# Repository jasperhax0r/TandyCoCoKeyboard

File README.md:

<!-- 
[![Contributors][contributors-shield]][contributors-url]
[![Forks][forks-shield]][forks-url]
[![Stargazers][stars-shield]][stars-url]
[![Issues][issues-shield]][issues-url]
[![License][license-shield]][license-url]
[![LinkedIn][linkedin-shield]][linkedin-url] -->

![Tandy CoCo2 Keyboard][product-screenshot]

* [Choose an Open Source License](https://choosealicense.com)
<!--  * [Img Shields](https://shields.io) -->
* [GitHub Pages](https://pages.github.com)

<!-- [contributors-shield]: https://img.shields.io/github/contributors/othneildrew/Best-README-Template.svg?style=for-the-badge
[contributors-url]: https://github.com/jasperhax0r/TandyCoCoKeyboard/graphs/contributors
[forks-shield]: https://img.shields.io/github/forks/othneildrew/Best-README-Template.svg?style=for-the-badge
[forks-url]: https://github.com/jasperhax0r/TandyCoCoKeyboard/network/members
[stars-shield]: https://img.shields.io/github/stars/othneildrew/Best-README-Template.svg?style=for-the-badge
[stars-url]: https://github.com/jasperhax0r/TandyCoCoKeyboard/stargazers
[issues-shield]: https://img.shields.io/github/issues/othneildrew/Best-README-Template.svg?style=for-the-badge
[issues-url]: https://github.com/jasperhax0r/TandyCoCoKeyboard/issues
[license-shield]: https://img.shields.io/github/license/jasperhax0r/TandyCoCoKeyboard?style=for-the-badge
[license-url]: https://github.com/jasperhax0r/TandyCoCoKeyboard/blob/main/LICENSE
[linkedin-shield]: https://img.shields.io/badge/-LinkedIn-black.svg?style=for-the-badge&logo=linkedin&colorB=555
[linkedin-url]: https://linkedin.com/in/othneildrew](https://www.linkedin.com/in/jasper-johnson-922b7330/
 -->
[product-screenshot]: images/3dview.png

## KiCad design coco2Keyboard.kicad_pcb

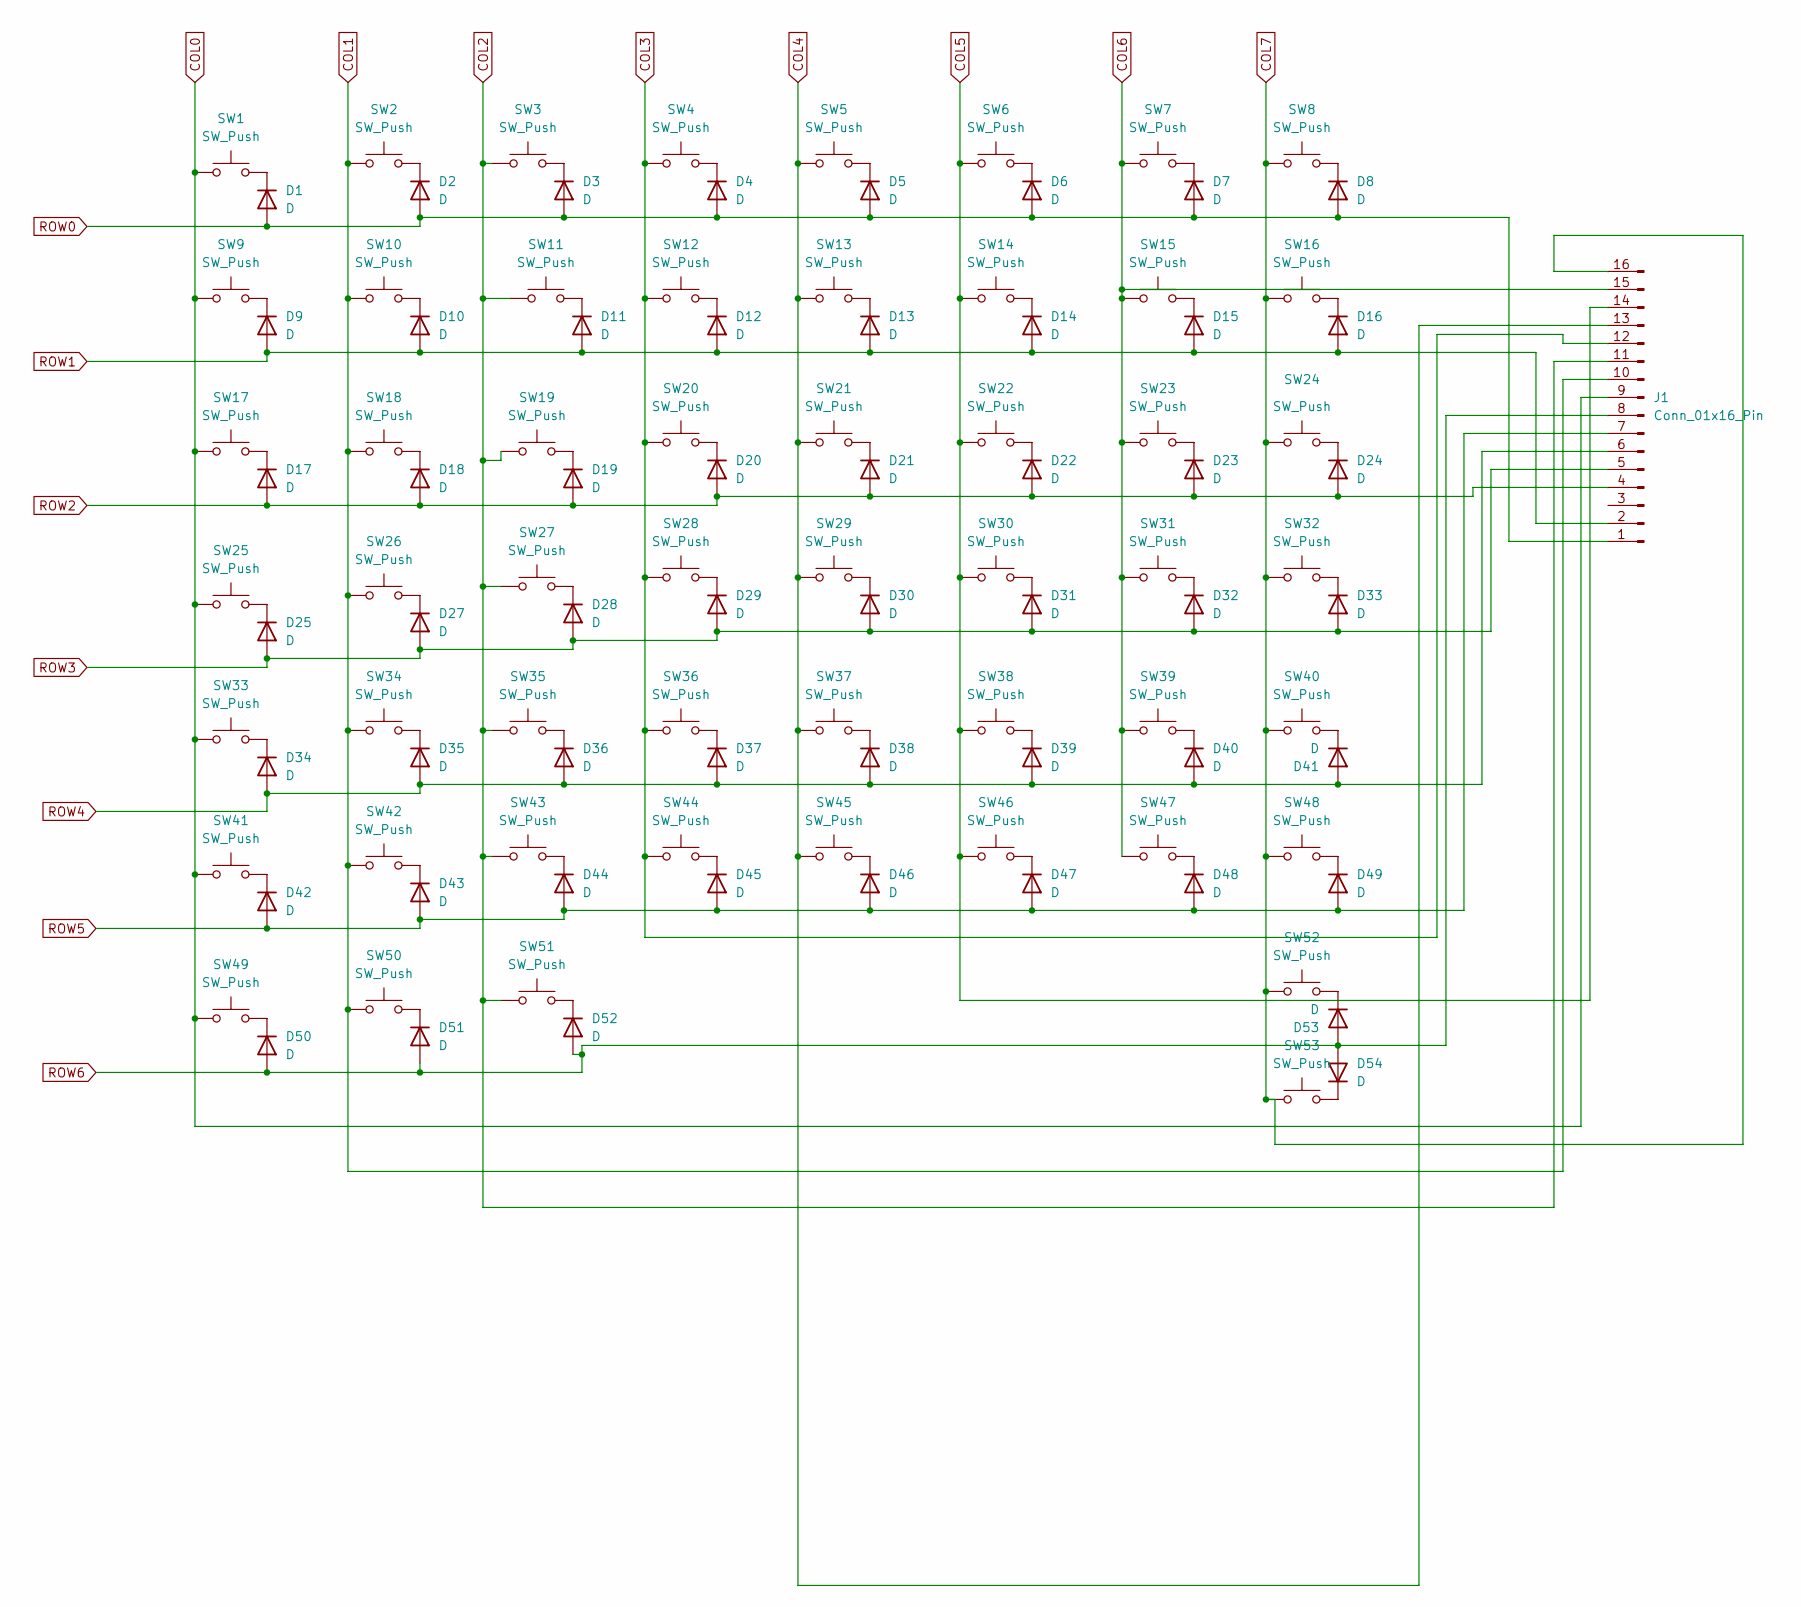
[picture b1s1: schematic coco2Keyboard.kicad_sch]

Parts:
D1, D2, D3, D4, D5, D6, D7, D8, D9, D10, D11, D12, D13, D14, D15, D16, D17, D18, D19, D20, D21, D22, D23, D24, D25, D27, D28, D29, D30, D31, D32, D33, D34, D35, D36, D37, D38, D39, D40, D41, D42, D43, D44, D45, D46, D47, D48, D49, D50, D51, D52, D53, D54: D; D_SOD-123
J1: Conn_01x16_Pin; PinHeader_1x16_P2.54mm_Horizontal
SW1, SW2, SW3, SW4, SW5, SW6, SW7, SW8, SW9, SW10, SW11, SW12, SW13, SW14, SW15, SW16, SW17, SW18, SW19, SW20, SW21, SW22, SW23, SW24, SW25, SW26, SW27, SW28, SW29, SW30, SW31, SW33, SW34, SW35, SW36, SW37, SW38, SW39, SW40, SW41, SW42, SW43, SW44, SW45, SW46, SW47, SW48, SW50, SW51: SW_Push; SW_Cherry_MX_1.00u_PCB
SW32: SW_Push; SW_Cherry_MX_6.25u_PCB
SW49: SW_Push; SW_Cherry_MX_2.25u_PCB
SW52, SW53: SW_Push; SW_Cherry_MX_1.75u_PCB

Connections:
COL0: J1.9, SW1.1, SW9.1, SW17.1, SW25.1, SW33.1, SW41.1, SW49.1
COL1: J1.10, SW2.1, SW10.1, SW18.1, SW26.1, SW34.1, SW42.1, SW50.1
COL2: J1.11, SW3.1, SW11.1, SW19.1, SW27.1, SW35.1, SW43.1, SW51.1
COL3: J1.12, SW4.1, SW12.1, SW20.1, SW28.1, SW36.1, SW44.1
COL4: J1.13, SW5.1, SW13.1, SW21.1, SW29.1, SW37.1, SW45.1
COL5: J1.14, SW6.1, SW14.1, SW22.1, SW30.1, SW38.1, SW46.1
COL6: J1.15, SW7.1, SW15.1, SW23.1, SW31.1, SW39.1, SW47.1
COL7: J1.16, SW8.1, SW16.1, SW24.1, SW32.1, SW40.1, SW48.1, SW52.1, SW53.1
unnamed: D1.1 (K), SW1.2
unnamed: D2.1 (K), SW2.2
unnamed: D3.1 (K), SW3.2
unnamed: D4.1 (K), SW4.2
unnamed: D5.1 (K), SW5.2
unnamed: D6.1 (K), SW6.2
unnamed: D7.1 (K), SW7.2
unnamed: D8.1 (K), SW8.2
unnamed: D9.1 (K), SW9.2
unnamed: D10.1 (K), SW10.2
unnamed: D11.1 (K), SW11.2
unnamed: D12.1 (K), SW12.2
unnamed: D13.1 (K), SW13.2
unnamed: D14.1 (K), SW14.2
unnamed: D15.1 (K), SW15.2
unnamed: D16.1 (K), SW16.2
unnamed: D17.1 (K), SW17.2
unnamed: D18.1 (K), SW18.2
unnamed: D19.1 (K), SW19.2
unnamed: D20.1 (K), SW20.2
unnamed: D21.1 (K), SW21.2
unnamed: D22.1 (K), SW22.2
unnamed: D23.1 (K), SW23.2
unnamed: D24.1 (K), SW24.2
unnamed: D25.1 (K), SW25.2
unnamed: D27.1 (K), SW26.2
unnamed: D28.1 (K), SW27.2
unnamed: D29.1 (K), SW28.2
unnamed: D30.1 (K), SW29.2
unnamed: D31.1 (K), SW30.2
unnamed: D32.1 (K), SW31.2
unnamed: D33.1 (K), SW32.2
unnamed: D34.1 (K), SW33.2
unnamed: D35.1 (K), SW34.2
unnamed: D36.1 (K), SW35.2
unnamed: D37.1 (K), SW36.2
unnamed: D38.1 (K), SW37.2
unnamed: D39.1 (K), SW38.2
unnamed: D40.1 (K), SW39.2
unnamed: D41.1 (K), SW40.2
unnamed: D42.1 (K), SW41.2
unnamed: D43.1 (K), SW42.2
unnamed: D44.1 (K), SW43.2
unnamed: D45.1 (K), SW44.2
unnamed: D46.1 (K), SW45.2
unnamed: D47.1 (K), SW46.2
unnamed: D48.1 (K), SW47.2
unnamed: D49.1 (K), SW48.2
unnamed: D50.1 (K), SW49.2
unnamed: D51.1 (K), SW50.2
unnamed: D52.1 (K), SW51.2
unnamed: D53.1 (K), SW52.2
unnamed: D54.1 (K), SW53.2
ROW0: D1.2 (A), D2.2 (A), D3.2 (A), D4.2 (A), D5.2 (A), D6.2 (A), D7.2 (A), D8.2 (A), J1.1
ROW1: D9.2 (A), D10.2 (A), D11.2 (A), D12.2 (A), D13.2 (A), D14.2 (A), D15.2 (A), D16.2 (A), J1.2
ROW2: D17.2 (A), D18.2 (A), D19.2 (A), D20.2 (A), D21.2 (A), D22.2 (A), D23.2 (A), D24.2 (A), J1.4
ROW3: D25.2 (A), D27.2 (A), D28.2 (A), D29.2 (A), D30.2 (A), D31.2 (A), D32.2 (A), D33.2 (A), J1.5
ROW4: D34.2 (A), D35.2 (A), D36.2 (A), D37.2 (A), D38.2 (A), D39.2 (A), D40.2 (A), D41.2 (A), J1.6
ROW5: D42.2 (A), D43.2 (A), D44.2 (A), D45.2 (A), D46.2 (A), D47.2 (A), D48.2 (A), D49.2 (A), J1.7
ROW6: D50.2 (A), D51.2 (A), D52.2 (A), D53.2 (A), D54.2 (A), J1.8

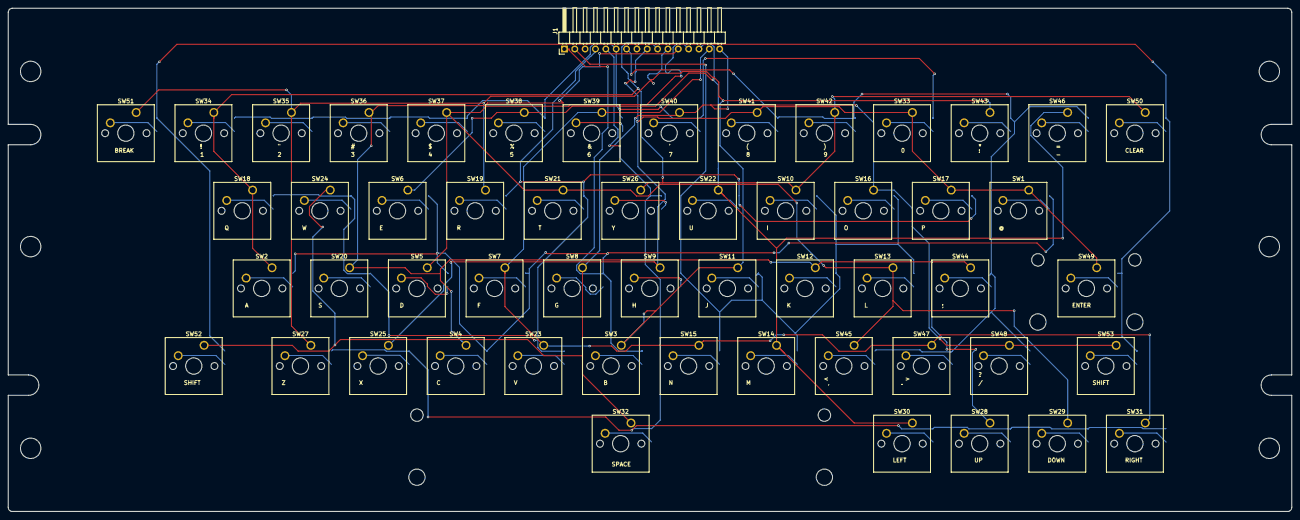
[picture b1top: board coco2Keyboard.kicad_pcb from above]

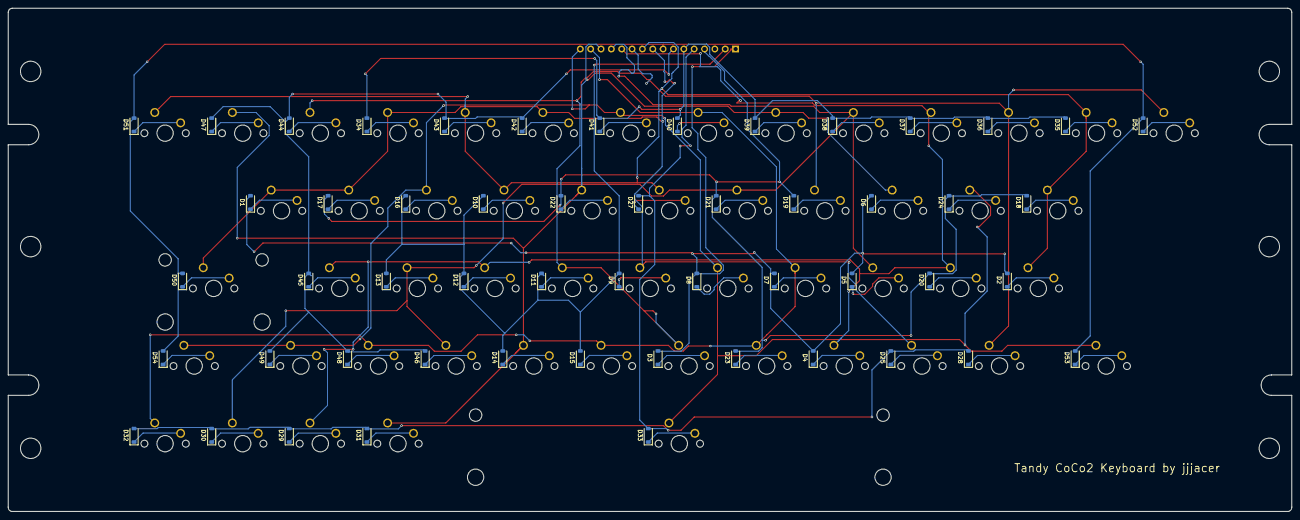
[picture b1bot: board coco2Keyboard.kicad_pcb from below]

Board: 2 copper layers, 315.0 x 123.5 mm, 113 parts (53 on the bottom side), 68 nets.

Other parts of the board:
Mount1, Mount2, Mount3, Mount4, Mount5, Mount6: MountingHole_5mm

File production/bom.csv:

Designator,Footprint,Quantity,Value,LCSC Part #
"D1, D10, D11, D12, D13, D14, D15, D16, D17, D18, D19, D2, D20, D21, D22, D23, D24, D25, D27, D28, D29, D3, D30, D31, D32, D33, D34, D35, D36, D37, D38, D39, D4, D40, D41, D42, D43, D44, D45, D46, D47, D48, D49, D5, D50, D51, D52, D53, D54, D6, D7, D8, D9",D_SOD-123,53,D,
J1,PinHeader_1x16_P2.54mm_Horizontal,1,Conn_01x16_Pin,
"SW1, SW10, SW11, SW12, SW13, SW14, SW15, SW16, SW17, SW18, SW19, SW2, SW20, SW21, SW22, SW23, SW24, SW25, SW26, SW27, SW28, SW29, SW3, SW30, SW31, SW33, SW34, SW35, SW36, SW37, SW38, SW39, SW4, SW40, SW41, SW42, SW43, SW44, SW45, SW46, SW47, SW48, SW5, SW50, SW51, SW6, SW7, SW8, SW9",SW_Cherry_MX_1.00u_PCB,49,SW_Push,
SW32,SW_Cherry_MX_6.25u_PCB,1,SW_Push,
SW49,SW_Cherry_MX_2.25u_PCB,1,SW_Push,
"SW52, SW53",SW_Cherry_MX_1.75u_PCB,2,SW_Push,

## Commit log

2025-06-03 Upload of first revision of keyboard PCB
